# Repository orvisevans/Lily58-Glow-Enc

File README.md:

# Lily58 × qtkb Glow + Rotary Encoders

This is still very much under active development. I've ordered the pcb and parts and am waiting for them to arrive. Since then, I've found some incompatibilities between the design and product list. I've not yet tested in the real world or worked out there bugs.

Lily58 is 6×4+4keys column-staggered split keyboard.
This fork adds an encoder to the key below the controller.

I got this board manufactured by JLCPCB. Just upload the file called gerber.zip to their quote tool, choose how many (5 is minimum), choose your color, (default options are fine) and order! Mine were $8.40 for a set of 5 and $9.03 shipping in July 2020.

If you don't want underglow, bridge dio from the first underglow led (L34) to the first led of the keys (L1) and update the code accordingly.

This picture is from the original Lily58 Glow. Pictures of this project are forthcoming.

## PCB Front

## PCB Back

# Parts

| Part Name                    | Quantity | Link                                                                                                                                                                                                                                                                                          | Price/Unit | Total    |
| ---------------------------- | -------- | --------------------------------------------------------------------------------------------------------------------------------------------------------------------------------------------------------------------------------------------------------------------------------------------- | ---------- | -------- |
| Lily58L PCB                  | 2        | JLCPCB                                                                                                                                                                                                                                                                                        | \$8.72     | \$17.43  |
| Lily58L Case                 | 1        | Using 2 more circuit boards as the bottom. No other case for now.                                                                                                                                                                                                                             | \$0.00     | \$0.00   |
| Pro Micro                    | 2        | https://www.aliexpress.com/item/32888212119.html?spm=a2g0o.productlist.0.0.30d25a53xh6DaX&algo_pvid=9e5fb73d-c3e5-475f-bda1-b4666011fa38&algo_expid=9e5fb73d-c3e5-475f-bda1-b4666011fa38-8&btsid=0ab6f82215936295153445783e35b6&ws_ab_test=searchweb0_0,searchweb201602_,searchweb201603_     | \$5.59     | \$11.17  |
| Micro USB Cable              | 2        | --                                                                                                                                                                                                                                                                                            | \$0.00     | \$0.00   |
| OLED module                  | 2        | https://www.aliexpress.com/item/32861875681.html?spm=a2g0o.productlist.0.0.835aa9ccjrnsdV&algo_pvid=7def10f1-db5f-4a13-951c-5bf7341c096e&algo_expid=7def10f1-db5f-4a13-951c-5bf7341c096e-0&btsid=0ab6d69f15936287684868637e6e79&ws_ab_test=searchweb0_0,searchweb201602_,searchweb201603_     | \$1.96     | \$3.92   |
| Rotary Encoder               | 2        | https://www.aliexpress.com/item/32322425597.html?spm=a2g0o.productlist.0.0.6102314aqRHfGU&algo_pvid=281c4dc1-9caa-459f-8650-fbba7e4bec4d&algo_expid=281c4dc1-9caa-459f-8650-fbba7e4bec4d-9&btsid=0ab6d70515937408315558637e0bf2&ws_ab_test=searchweb0_0,searchweb201602_,searchweb201603_     | \$1.68     | \$3.35   |
| Knob                         | 2        | --                                                                                                                                                                                                                                                                                            |            | \$0.00   |
| Key switch (MX)              | 58       | https://www.aliexpress.com/item/32973993662.html?spm=a2g0o.productlist.0.0.6fdb14ebdXgCiL&algo_pvid=dc98baa5-021b-42b9-806a-ef67fe903a97&algo_expid=dc98baa5-021b-42b9-806a-ef67fe903a97-10&btsid=0ab6d69515936249739887508eaca4&ws_ab_test=searchweb0_0,searchweb201602_,searchweb201603_    | \$0.29     | \$16.99  |
| Kailh switch socket          | 58       | https://www.aliexpress.com/item/10000252734106.html?spm=a2g0o.productlist.0.0.6b9a1faaM3DsBf&algo_pvid=aa995bed-9941-44f5-8e5d-accedfc3bf1e&algo_expid=aa995bed-9941-44f5-8e5d-accedfc3bf1e-10&btsid=0be3743615936252288275769e1733&ws_ab_test=searchweb0_0,searchweb201602_,searchweb201603_ | \$0.22     | \$12.90  |
| SK6812 Mini LEDs           | 60       | https://www.aliexpress.com/item/33019583218.html?spm=a2g0s.9042311.0.0.12a84c4dEvt2eo   | \$0.18     | \$10.71  |
| SK6812 Mini LEDs             | 12       | Use the above link                                                                                                                                                                                                                                                  |            | \$0.00   |
| Diodes 1N4148 (Through-hole) | 58       | https://www.aliexpress.com/item/1934432186.html?spm=a2g0o.productlist.0.0.43075a93S1HiAy&algo_pvid=2a96b464-fcb2-4d4d-9db0-5325780cc08b&algo_expid=2a96b464-fcb2-4d4d-9db0-5325780cc08b-2&btsid=0ab6f82415937472454356384e6daf&ws_ab_test=searchweb0_0,searchweb201602_,searchweb201603_      | \$0.04     | \$2.48   |
| TRRS Jack                    | 2        | https://www.aliexpress.com/item/33029465106.html?spm=a2g0o.productlist.0.0.4c934e0cJHeHoK&algo_pvid=eae4b36e-738c-4df6-8e73-ad7bf5885647&algo_expid=eae4b36e-738c-4df6-8e73-ad7bf5885647-0&btsid=0ab6fab215936264228847161e1394&ws_ab_test=searchweb0_0,searchweb201602_,searchweb201603_     | \$1.63     | \$3.26   |
| TRRS Cable                   | 1        | https://www.aliexpress.com/item/33000197351.html?spm=a2g0o.productlist.0.0.21a2246ecsIFwV&algo_pvid=fd7c3341-82d4-4c30-813e-1d52c9431132&algo_expid=fd7c3341-82d4-4c30-813e-1d52c9431132-3&btsid=0ab6fab215936268107442907e1395&ws_ab_test=searchweb0_0,searchweb201602_,searchweb201603_     | \$1.79     | \$1.79   |
| Tactile switch               | 0        | Needed but not sourced.                                                                                                                                                                                                                                                                       |            | \$0.00   |
| Key Caps                     | 58       | https://www.aliexpress.com/item/32744591039.html?spm=a2g0o.cart.0.0.1fff3c00zqG7Sv&mp=1                                                                                                                                                                                                       | \$0.44     | \$25.5   |
| M2 Standoffs                 | 14       | https://www.aliexpress.com/item/32839434178.html?spm=a2g0o.productlist.0.0.55a049d0Wpvk4j&algo_pvid=b7593b96-f169-4b42-9f04-20554ae42bde&algo_expid=b7593b96-f169-4b42-9f04-20554ae42bde-19&btsid=0ab6f83115936383891028466e7acb&ws_ab_test=searchweb0_0,searchweb201602_,searchweb201603_    | \$0.57     | \$7.99   |
| M2 Screws                    | 28       | https://www.aliexpress.com/item/32730208891.html?spm=2114.12010612.8148356.21.445e15ccXDyc9g                                                                                                                                                                                                  | \$0.21     | \$5.74   |
|                              |          |                                                                                                                                                                                                                                                                                               | Total:     | \$115.80 |

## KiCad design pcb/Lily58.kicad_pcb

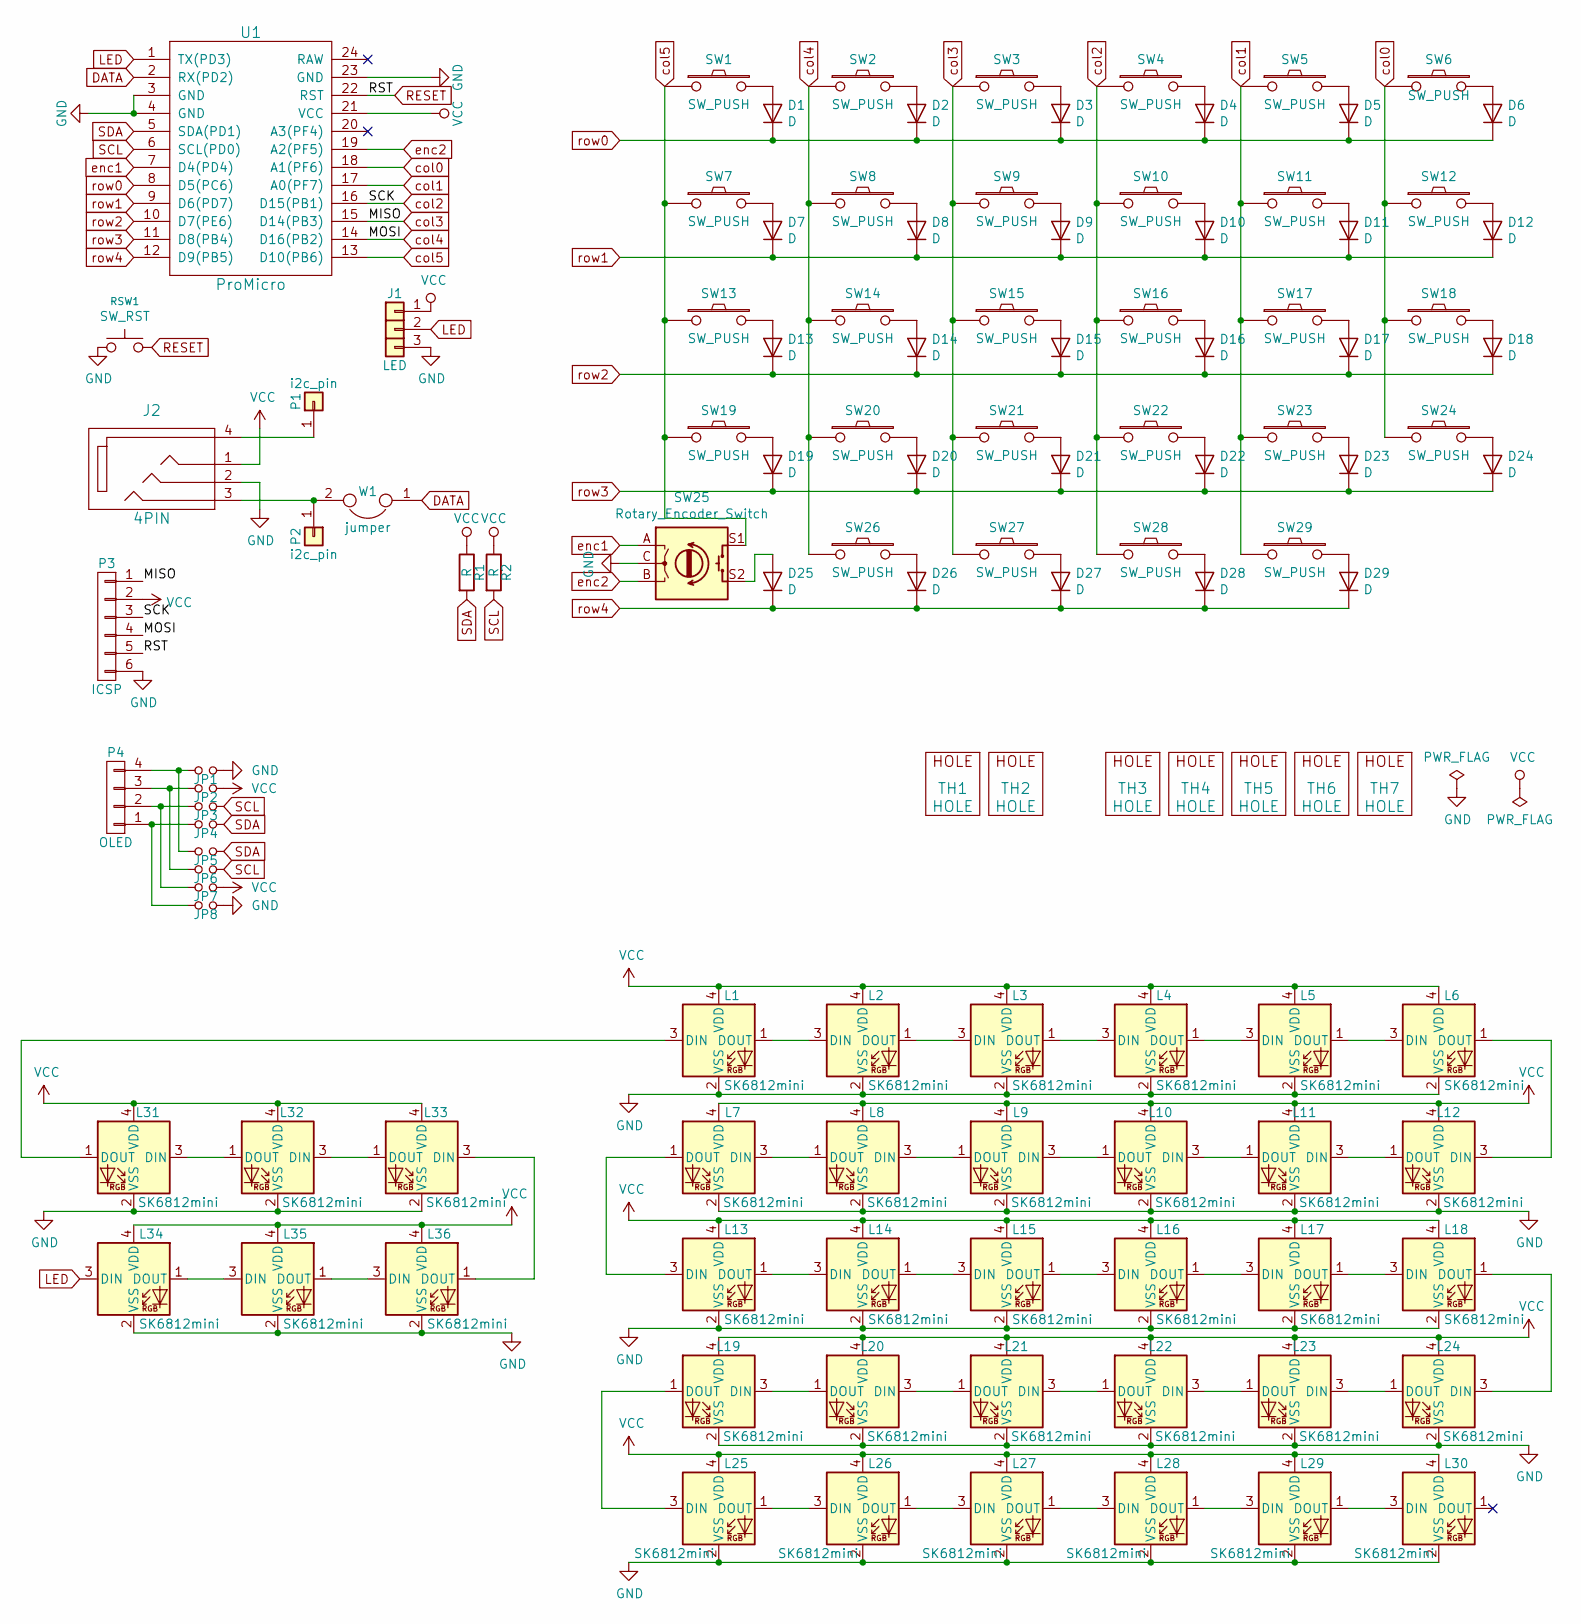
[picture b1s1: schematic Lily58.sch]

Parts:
D1, D2, D3, D4, D5, D6, D7, D8, D9, D10, D11, D12, D13, D14, D15, D16, D17, D18, D19, D20, D21, D22, D23, D24, D25, D26, D27, D28, D29: D; Diode_TH_SOD123
J1: LED; StripLED
J2: 4PIN; MJ-4PP-9
JP1, JP2, JP3, JP4, JP5, JP6, JP7, JP8: Jumper_NO_Small; Jumper
L1, L2, L3, L4, L5, L6, L7, L8, L9, L10, L11, L12, L13, L14, L15, L16, L17, L18, L19, L20, L21, L22, L23, L24, L25, L26, L27, L28, L29, L30: SK6812mini; SK6812MINI_rev
L31, L32, L33, L34, L35, L36: SK6812mini; SK6812MINI_underglow_rev
P1, P2: i2c_pin; 1pin_conn
P3: ICSP
P4: OLED; MY_SIL-4
R1, R2: R; RESISTOR_mini
RSW1: SW_RST; TACT_SWITCH_TVBP06
SW1, SW2, SW3, SW4, SW5, SW6, SW7, SW8, SW9, SW10, SW11, SW12, SW13, SW14, SW15, SW16, SW17, SW18, SW19, SW20, SW21, SW22, SW23, SW24, SW27, SW28, SW29: SW_PUSH; MX_PG1350_FLIP_HOLES_18mm
SW25: Rotary_Encoder_Switch; RotaryEncoder_Alps_EC11E-Switch_Vertical_H20mm
SW26: SW_PUSH; MX_PG1350_FLIP_HOLES_27mm
TH1, TH2: HOLE; HOLE_M2
TH3, TH4, TH5, TH6, TH7: HOLE; HOLE_M2_TH
U1: ProMicro; ProMicro_rev2
W1: jumper; jumper_data

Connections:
DATA: U1.2 (RX(PD2)), W1.1
GND: J1.3, J2.2, JP1.2, JP8.2, L1.2 (VSS), L2.2 (VSS), L3.2 (VSS), L4.2 (VSS), L5.2 (VSS), L6.2 (VSS), L7.2 (VSS), L8.2 (VSS), L9.2 (VSS), L10.2 (VSS), L11.2 (VSS), L12.2 (VSS), L13.2 (VSS), L14.2 (VSS), L15.2 (VSS), L16.2 (VSS), L17.2 (VSS), L18.2 (VSS), L19.2 (VSS), L20.2 (VSS), L21.2 (VSS), L22.2 (VSS), L23.2 (VSS), L24.2 (VSS), L25.2 (VSS), L26.2 (VSS), L27.2 (VSS), L28.2 (VSS), L29.2 (VSS), L30.2 (VSS), L31.2 (VSS), L32.2 (VSS), L33.2 (VSS), L34.2 (VSS), L35.2 (VSS), L36.2 (VSS), P3.6, RSW1.1, SW25.C, U1.3 (GND), U1.4 (GND), U1.23 (GND)
LED: J1.2, L34.3 (DIN), U1.1 (TX(PD3))
unnamed: D1.2 (A), SW1.2
unnamed: D2.2 (A), SW2.2
unnamed: D3.2 (A), SW3.2
unnamed: D4.2 (A), SW4.2
unnamed: D5.2 (A), SW5.2
unnamed: D6.2 (A), SW6.2
unnamed: D7.2 (A), SW7.2
unnamed: D8.2 (A), SW8.2
unnamed: D9.2 (A), SW9.2
unnamed: D10.2 (A), SW10.2
unnamed: D11.2 (A), SW11.2
unnamed: D12.2 (A), SW12.2
unnamed: D13.2 (A), SW13.2
unnamed: D14.2 (A), SW14.2
unnamed: D15.2 (A), SW15.2
unnamed: D16.2 (A), SW16.2
unnamed: D17.2 (A), SW17.2
unnamed: D18.2 (A), SW18.2
unnamed: D19.2 (A), SW19.2
unnamed: D20.2 (A), SW20.2
unnamed: D21.2 (A), SW21.2
unnamed: D22.2 (A), SW22.2
unnamed: D23.2 (A), SW23.2
unnamed: D24.2 (A), SW24.2
unnamed: D25.2 (A), SW25.S2
unnamed: D26.2 (A), SW26.2
unnamed: D27.2 (A), SW27.2
unnamed: D28.2 (A), SW28.2
unnamed: D29.2 (A), SW29.2
unnamed: J2.3, P2.1, W1.2
unnamed: J2.4, P1.1
unnamed: JP1.1, JP5.1, P4.4
unnamed: JP2.1, JP6.1, P4.3
unnamed: JP3.1, JP7.1, P4.2
unnamed: JP4.1, JP8.1, P4.1
unnamed: L1.1 (DOUT), L2.3 (DIN)
unnamed: L1.3 (DIN), L31.1 (DOUT)
unnamed: L2.1 (DOUT), L3.3 (DIN)
unnamed: L3.1 (DOUT), L4.3 (DIN)
unnamed: L4.1 (DOUT), L5.3 (DIN)
unnamed: L5.1 (DOUT), L6.3 (DIN)
unnamed: L7.3 (DIN), L8.1 (DOUT)
unnamed: L8.3 (DIN), L9.1 (DOUT)
unnamed: L9.3 (DIN), L10.1 (DOUT)
unnamed: L10.3 (DIN), L11.1 (DOUT)
unnamed: L11.3 (DIN), L12.1 (DOUT)
unnamed: L6.1 (DOUT), L12.3 (DIN)
unnamed: L13.1 (DOUT), L14.3 (DIN)
unnamed: L7.1 (DOUT), L13.3 (DIN)
unnamed: L14.1 (DOUT), L15.3 (DIN)
unnamed: L15.1 (DOUT), L16.3 (DIN)
unnamed: L16.1 (DOUT), L17.3 (DIN)
unnamed: L17.1 (DOUT), L18.3 (DIN)
unnamed: L18.1 (DOUT), L24.3 (DIN)
unnamed: L19.1 (DOUT), L25.3 (DIN)
unnamed: L19.3 (DIN), L20.1 (DOUT)
unnamed: L20.3 (DIN), L21.1 (DOUT)
unnamed: L21.3 (DIN), L22.1 (DOUT)
unnamed: L22.3 (DIN), L23.1 (DOUT)
unnamed: L23.3 (DIN), L24.1 (DOUT)
unnamed: L25.1 (DOUT), L26.3 (DIN)
unnamed: L26.1 (DOUT), L27.3 (DIN)
unnamed: L27.1 (DOUT), L28.3 (DIN)
unnamed: L28.1 (DOUT), L29.3 (DIN)
unnamed: L29.1 (DOUT), L30.3 (DIN)
unnamed: L31.3 (DIN), L32.1 (DOUT)
unnamed: L32.3 (DIN), L33.1 (DOUT)
unnamed: L33.3 (DIN), L36.1 (DOUT)
unnamed: L34.1 (DOUT), L35.3 (DIN)
unnamed: L35.1 (DOUT), L36.3 (DIN)
RESET: P3.5, RSW1.2, U1.22 (RST)
SCL: JP3.2, JP6.2, R2.2, U1.6 (SCL(PD0))
SDA: JP4.2, JP5.2, R1.2, U1.5 (SDA(PD1))
VCC: J1.1, J2.1, JP2.2, JP7.2, L1.4 (VDD), L2.4 (VDD), L3.4 (VDD), L4.4 (VDD), L5.4 (VDD), L6.4 (VDD), L7.4 (VDD), L8.4 (VDD), L9.4 (VDD), L10.4 (VDD), L11.4 (VDD), L12.4 (VDD), L13.4 (VDD), L14.4 (VDD), L15.4 (VDD), L16.4 (VDD), L17.4 (VDD), L18.4 (VDD), L19.4 (VDD), L20.4 (VDD), L21.4 (VDD), L22.4 (VDD), L23.4 (VDD), L24.4 (VDD), L25.4 (VDD), L26.4 (VDD), L27.4 (VDD), L28.4 (VDD), L29.4 (VDD), L30.4 (VDD), L31.4 (VDD), L32.4 (VDD), L33.4 (VDD), L34.4 (VDD), L35.4 (VDD), L36.4 (VDD), P3.2, R1.1, R2.1, U1.21 (VCC)
col0: SW6.1, SW12.1, SW18.1, SW24.1, U1.18 (A1(PF6))
col1: SW5.1, SW11.1, SW17.1, SW23.1, SW29.1, U1.17 (A0(PF7))
col2: P3.3, SW4.1, SW10.1, SW16.1, SW22.1, SW28.1, U1.16 (D15(PB1))
col3: P3.1, SW3.1, SW9.1, SW15.1, SW21.1, SW27.1, U1.15 (D14(PB3))
col4: P3.4, SW2.1, SW8.1, SW14.1, SW20.1, SW26.1, U1.14 (D16(PB2))
col5: SW1.1, SW7.1, SW13.1, SW19.1, SW25.S1, U1.13 (D10(PB6))
enc1: SW25.A, U1.7 (D4(PD4))
enc2: SW25.B, U1.19 (A2(PF5))
row0: D1.1 (K), D2.1 (K), D3.1 (K), D4.1 (K), D5.1 (K), D6.1 (K), U1.8 (D5(PC6))
row1: D7.1 (K), D8.1 (K), D9.1 (K), D10.1 (K), D11.1 (K), D12.1 (K), U1.9 (D6(PD7))
row2: D13.1 (K), D14.1 (K), D15.1 (K), D16.1 (K), D17.1 (K), D18.1 (K), U1.10 (D7(PE6))
row3: D19.1 (K), D20.1 (K), D21.1 (K), D22.1 (K), D23.1 (K), D24.1 (K), U1.11 (D8(PB4))
row4: D25.1 (K), D26.1 (K), D27.1 (K), D28.1 (K), D29.1 (K), U1.12 (D9(PB5))

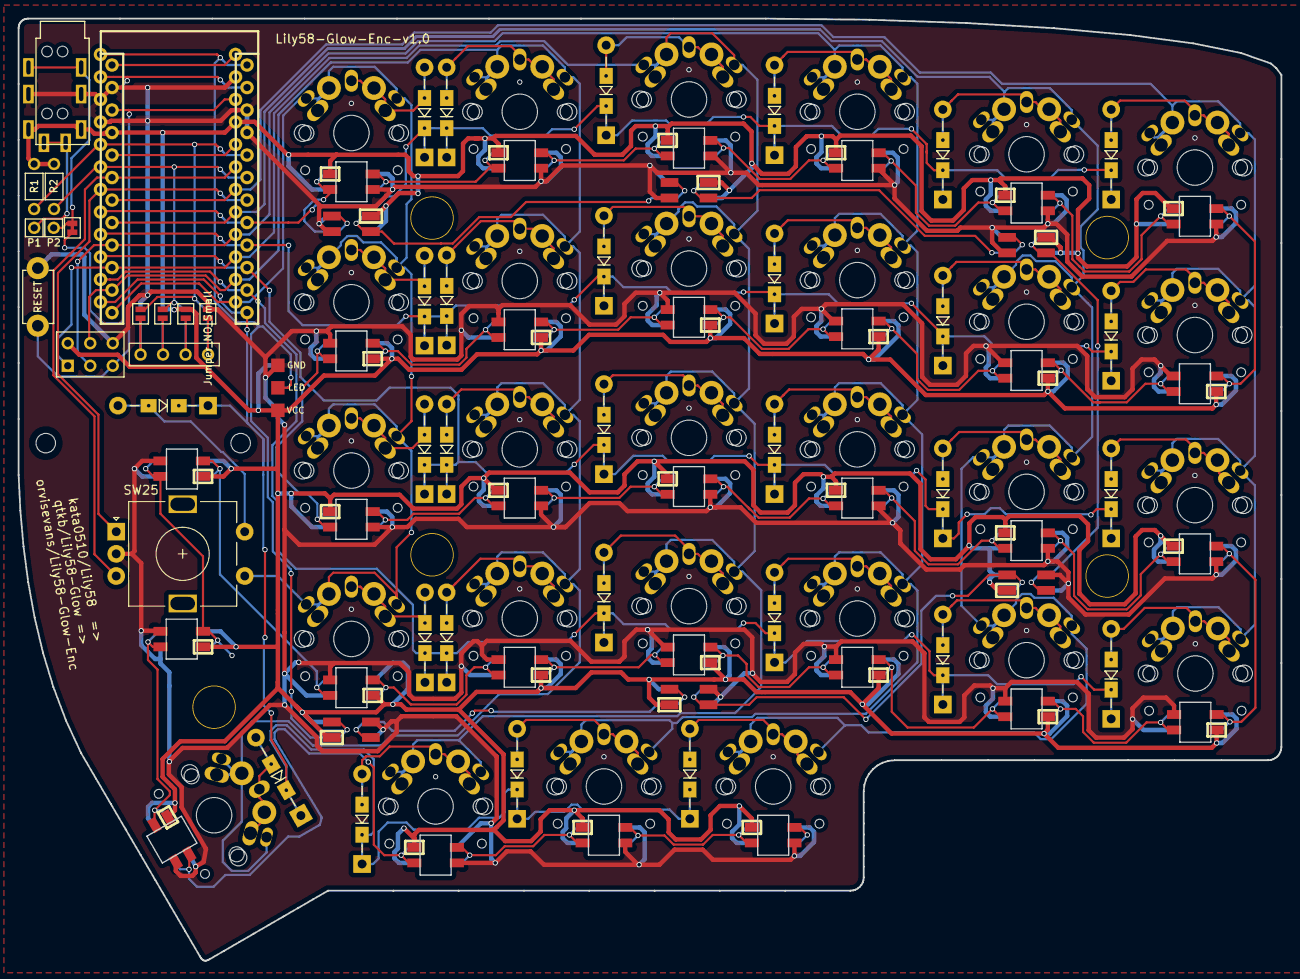
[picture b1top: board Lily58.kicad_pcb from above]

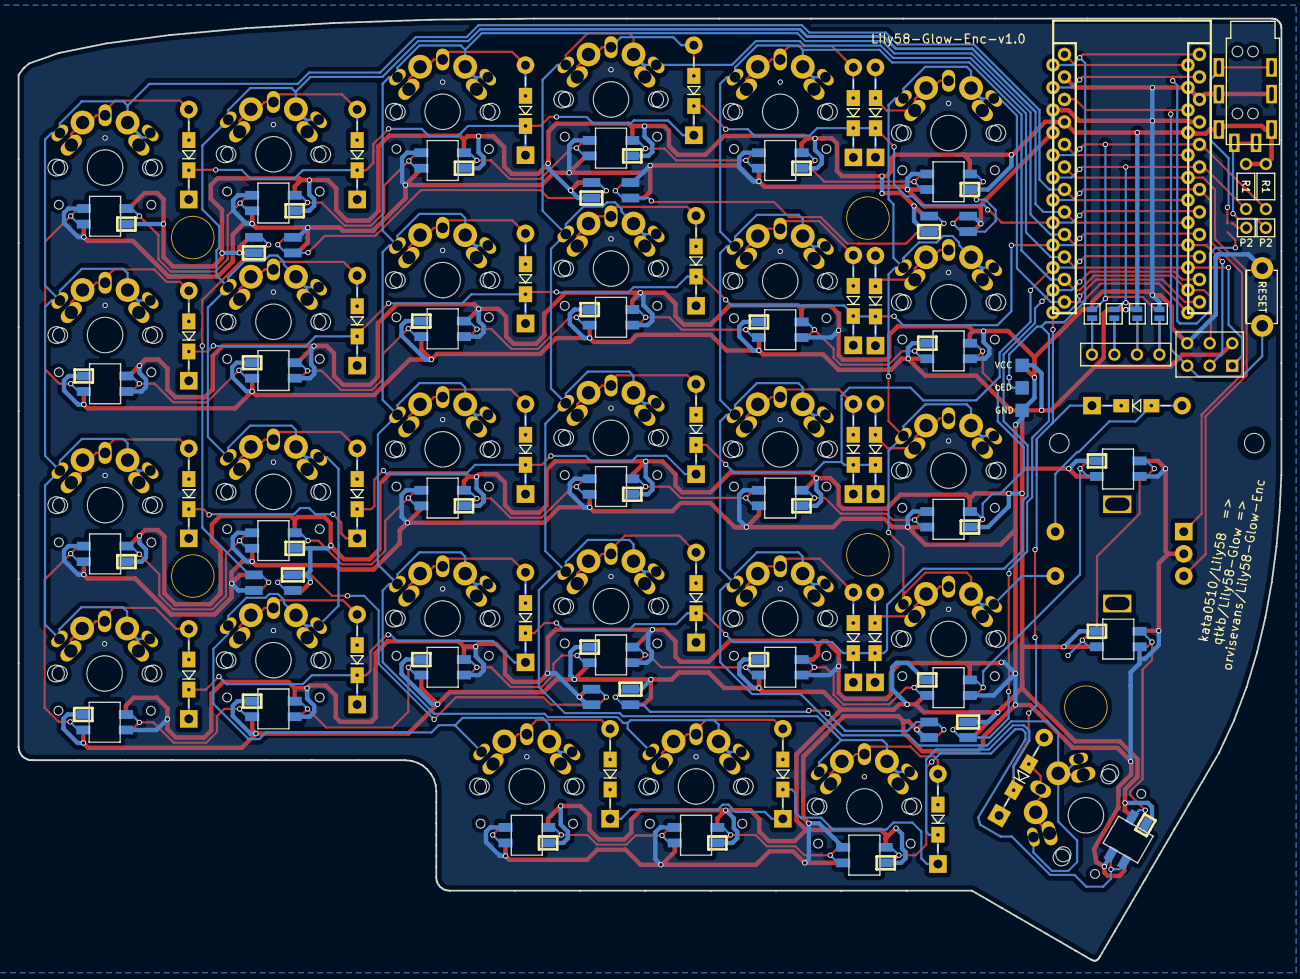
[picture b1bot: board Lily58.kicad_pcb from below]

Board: 2 copper layers, 142.5 x 106.3 mm, 120 parts (32 on the bottom side), 90 nets.

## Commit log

2020-07-01 Updated parts list
2020-07-03 Added Encoder and 1 led
2020-07-03 Updated README with new board
2020-07-03 Created gerbers
2020-07-03 One last board update
2020-07-03 Changed keycaps
2020-07-26 Update README.md
    Added disclaimer
2020-07-26 Update README.md
    Fixed some typos.
2021-04-26 Removed "e" from sk6812 mini.
